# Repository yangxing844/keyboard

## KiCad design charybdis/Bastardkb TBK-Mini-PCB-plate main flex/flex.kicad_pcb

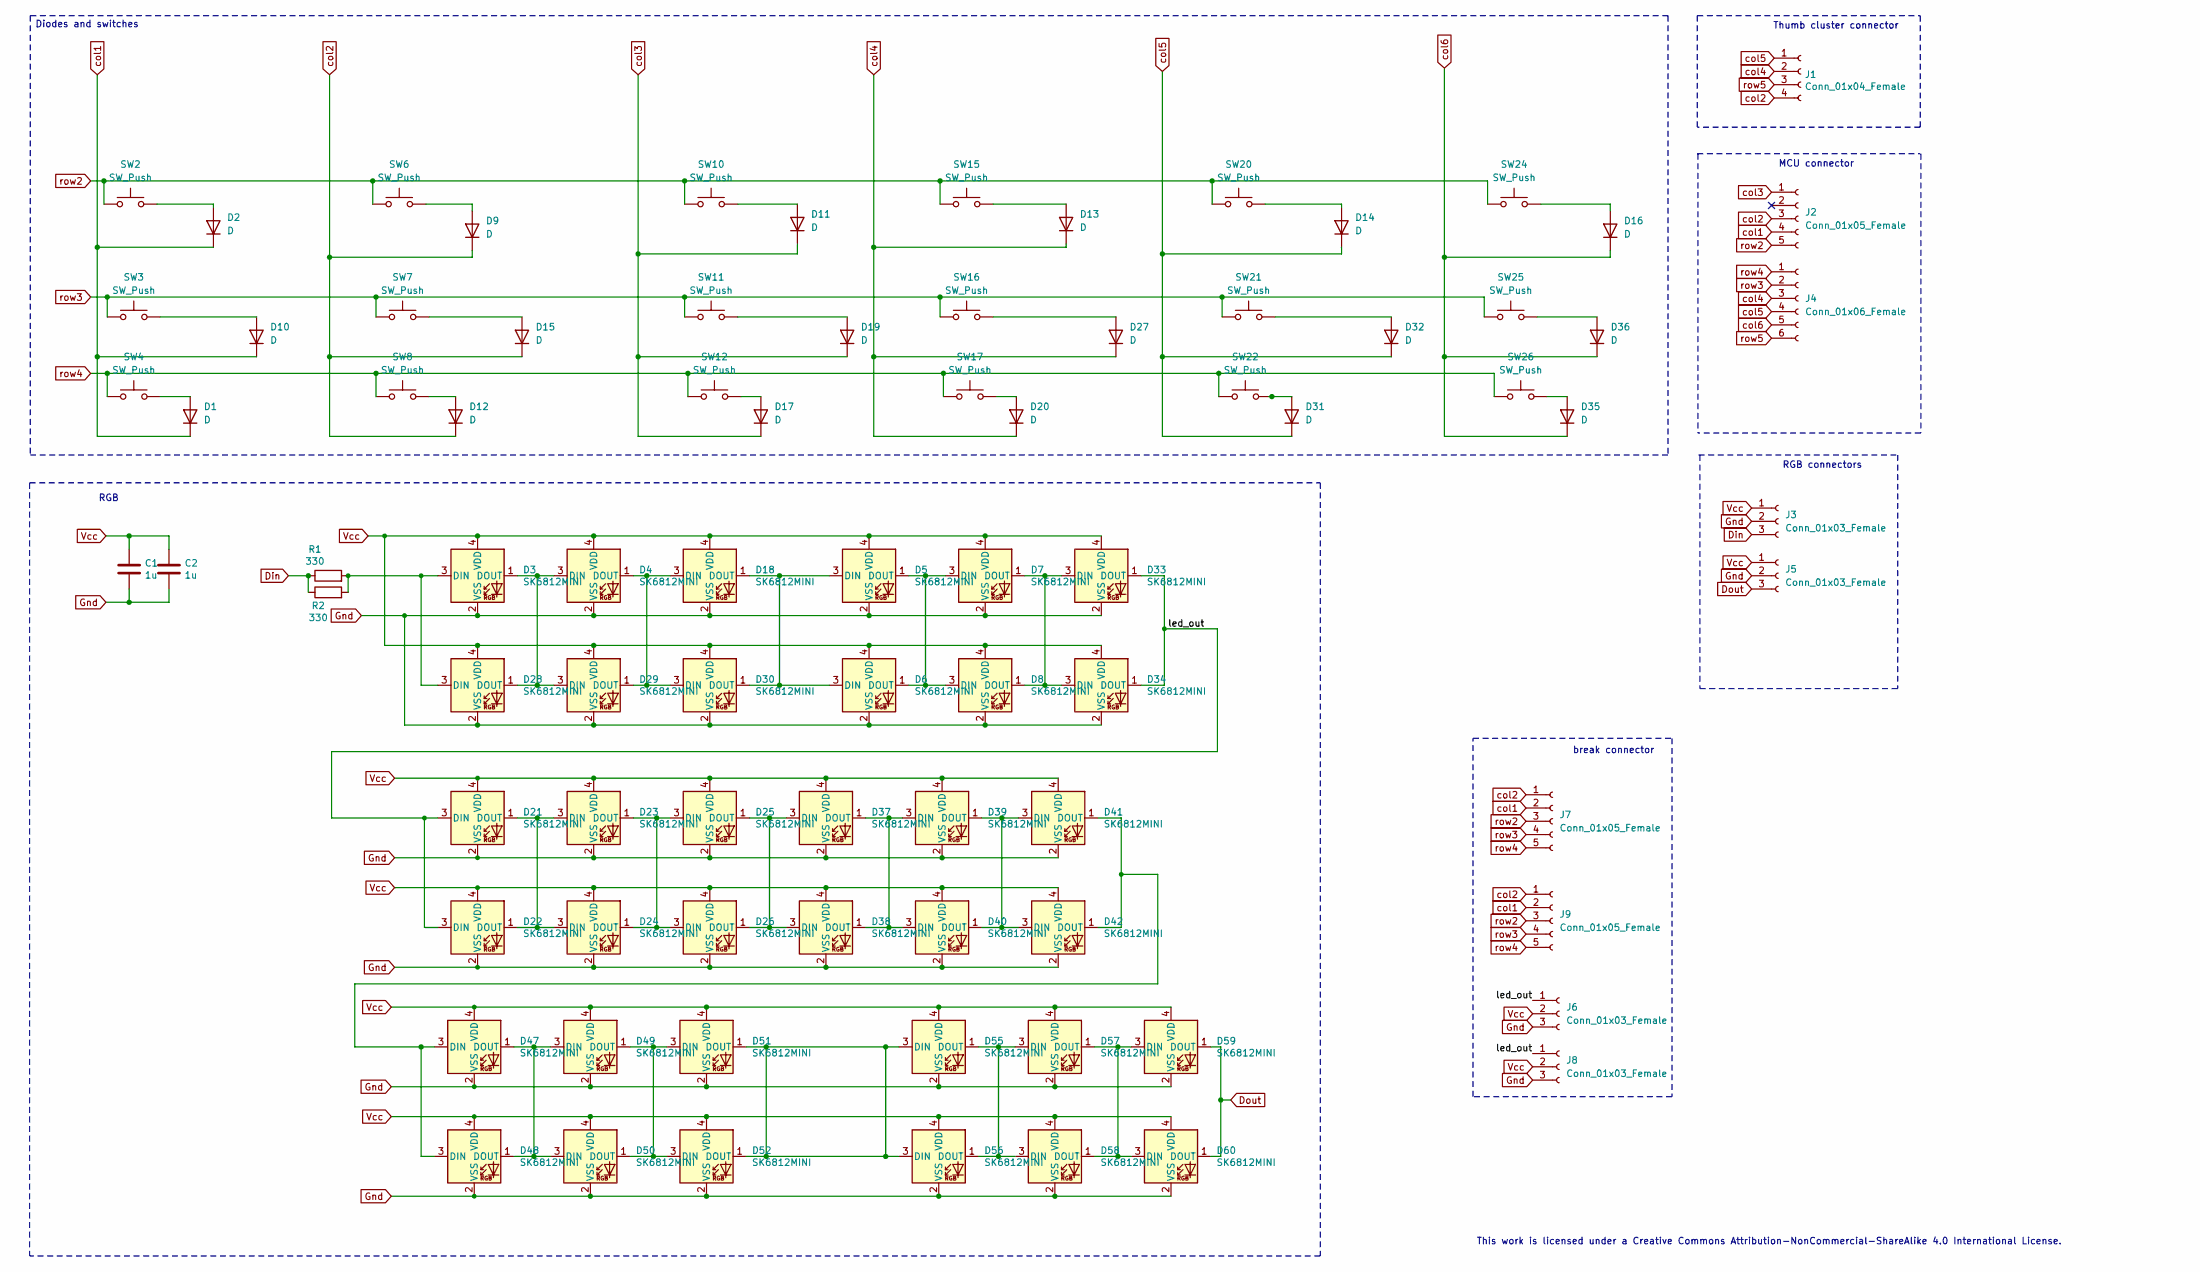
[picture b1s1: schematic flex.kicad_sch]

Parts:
C1, C2: 1u; C_1206_3216Metric_Pad1.42x1.75mm_HandSolder
D1, D2, D9, D10, D11, D12, D13, D14, D15, D16, D17, D19, D20, D27, D31, D32, D35, D36: D; Diode_TH_SOD123
D3, D4, D5, D7, D18, D21, D23, D25, D33, D37, D39, D41, D47, D49, D51, D55, D57, D59: SK6812MINI; YS-SK6812MINI-E_REVERSE
D6, D8, D22, D24, D26, D28, D29, D30, D34, D38, D40, D42, D48, D50, D52, D56, D58, D60: SK6812MINI; YS-SK6812MINI-E_REVERSE_NO_EDGECUT
J1: Conn_01x04_Female; PinHeader_1x04_P2.54mm_Vertical
J2, J7, J9: Conn_01x05_Female; PinHeader_1x05_P2.54mm_Vertical
J3, J5, J6, J8: Conn_01x03_Female; PinHeader_1x03_P2.54mm_Vertical
J4: Conn_01x06_Female; PinHeader_1x06_P2.54mm_Vertical
R1, R2: 330; R_1206_3216Metric_Pad1.42x1.75mm_HandSolder
SW2, SW3, SW4, SW6, SW7, SW8, SW10, SW11, SW12, SW15, SW16, SW17, SW20, SW21, SW22, SW24, SW25, SW26: SW_Push; keyswitch_cherrymx_hotswap_1u

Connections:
/led_out: D21.3 (DIN), D22.3 (DIN), D33.1 (DOUT), D34.1 (DOUT), J6.1, J8.1
Din: J3.3, R1.1, R2.1
Dout: D59.1 (DOUT), D60.1 (DOUT), J5.3
Gnd: C1.2, C2.2, D3.2 (VSS), D4.2 (VSS), D5.2 (VSS), D6.2 (VSS), D7.2 (VSS), D8.2 (VSS), D18.2 (VSS), D21.2 (VSS), D22.2 (VSS), D23.2 (VSS), D24.2 (VSS), D25.2 (VSS), D26.2 (VSS), D28.2 (VSS), D29.2 (VSS), D30.2 (VSS), D33.2 (VSS), D34.2 (VSS), D37.2 (VSS), D38.2 (VSS), D39.2 (VSS), D40.2 (VSS), D41.2 (VSS), D42.2 (VSS), D47.2 (VSS), D48.2 (VSS), D49.2 (VSS), D50.2 (VSS), D51.2 (VSS), D52.2 (VSS), D55.2 (VSS), D56.2 (VSS), D57.2 (VSS), D58.2 (VSS), D59.2 (VSS), D60.2 (VSS), J3.2, J5.2, J6.3, J8.3
unnamed: D1.2 (A), SW4.2
unnamed: D2.2 (A), SW2.2
unnamed: D5.1 (DOUT), D6.1 (DOUT), D7.3 (DIN), D8.3 (DIN)
unnamed: D9.2 (A), SW6.2
unnamed: D10.2 (A), SW3.2
unnamed: D11.2 (A), SW10.2
unnamed: D12.2 (A), SW8.2
unnamed: D13.2 (A), SW15.2
unnamed: D14.2 (A), SW20.2
unnamed: D15.2 (A), SW7.2
unnamed: D16.2 (A), SW24.2
unnamed: D17.2 (A), SW12.2
unnamed: D4.1 (DOUT), D18.3 (DIN), D29.1 (DOUT), D30.3 (DIN)
unnamed: D5.3 (DIN), D6.3 (DIN), D18.1 (DOUT), D30.1 (DOUT)
unnamed: D19.2 (A), SW11.2
unnamed: D20.2 (A), SW17.2
unnamed: D21.1 (DOUT), D22.1 (DOUT), D23.3 (DIN), D24.3 (DIN)
unnamed: D23.1 (DOUT), D24.1 (DOUT), D25.3 (DIN), D26.3 (DIN)
unnamed: D25.1 (DOUT), D26.1 (DOUT), D37.3 (DIN), D38.3 (DIN)
unnamed: D27.2 (A), SW16.2
unnamed: D3.3 (DIN), D28.3 (DIN), R1.2, R2.2
unnamed: D3.1 (DOUT), D4.3 (DIN), D28.1 (DOUT), D29.3 (DIN)
unnamed: D31.2 (A), SW22.2
unnamed: D32.2 (A), SW21.2
unnamed: D7.1 (DOUT), D8.1 (DOUT), D33.3 (DIN), D34.3 (DIN)
unnamed: D35.2 (A), SW26.2
unnamed: D36.2 (A), SW25.2
unnamed: D37.1 (DOUT), D38.1 (DOUT), D39.3 (DIN), D40.3 (DIN)
unnamed: D39.1 (DOUT), D40.1 (DOUT), D41.3 (DIN), D42.3 (DIN)
unnamed: D41.1 (DOUT), D42.1 (DOUT), D47.3 (DIN), D48.3 (DIN)
unnamed: D47.1 (DOUT), D48.1 (DOUT), D49.3 (DIN), D50.3 (DIN)
unnamed: D49.1 (DOUT), D50.1 (DOUT), D51.3 (DIN), D52.3 (DIN)
unnamed: D51.1 (DOUT), D52.1 (DOUT), D55.3 (DIN), D56.3 (DIN)
unnamed: D55.1 (DOUT), D56.1 (DOUT), D57.3 (DIN), D58.3 (DIN)
unnamed: D57.1 (DOUT), D58.1 (DOUT), D59.3 (DIN), D60.3 (DIN)
Vcc: C1.1, C2.1, D3.4 (VDD), D4.4 (VDD), D5.4 (VDD), D6.4 (VDD), D7.4 (VDD), D8.4 (VDD), D18.4 (VDD), D21.4 (VDD), D22.4 (VDD), D23.4 (VDD), D24.4 (VDD), D25.4 (VDD), D26.4 (VDD), D28.4 (VDD), D29.4 (VDD), D30.4 (VDD), D33.4 (VDD), D34.4 (VDD), D37.4 (VDD), D38.4 (VDD), D39.4 (VDD), D40.4 (VDD), D41.4 (VDD), D42.4 (VDD), D47.4 (VDD), D48.4 (VDD), D49.4 (VDD), D50.4 (VDD), D51.4 (VDD), D52.4 (VDD), D55.4 (VDD), D56.4 (VDD), D57.4 (VDD), D58.4 (VDD), D59.4 (VDD), D60.4 (VDD), J3.1, J5.1, J6.2, J8.2
col1: D1.1 (K), D2.1 (K), D10.1 (K), J2.4, J7.2, J9.2
col2: D9.1 (K), D12.1 (K), D15.1 (K), J1.4, J2.3, J7.1, J9.1
col3: D11.1 (K), D17.1 (K), D19.1 (K), J2.1
col4: D13.1 (K), D20.1 (K), D27.1 (K), J1.2, J4.3
col5: D14.1 (K), D31.1 (K), D32.1 (K), J1.1, J4.4
col6: D16.1 (K), D35.1 (K), D36.1 (K), J4.5
row2: J2.5, J7.3, J9.3, SW2.1, SW6.1, SW10.1, SW15.1, SW20.1, SW24.1
row3: J4.2, J7.4, J9.4, SW3.1, SW7.1, SW11.1, SW16.1, SW21.1, SW25.1
row4: J4.1, J7.5, J9.5, SW4.1, SW8.1, SW12.1, SW17.1, SW22.1, SW26.1
row5: J1.3, J4.6

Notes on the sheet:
break connector
RGB
Diodes and switches
Thumb cluster connector
RGB connectors
MCU connector
This work is licensed under a Creative Commons Attribution-NonCommercial-ShareAlike 4.0 International License.

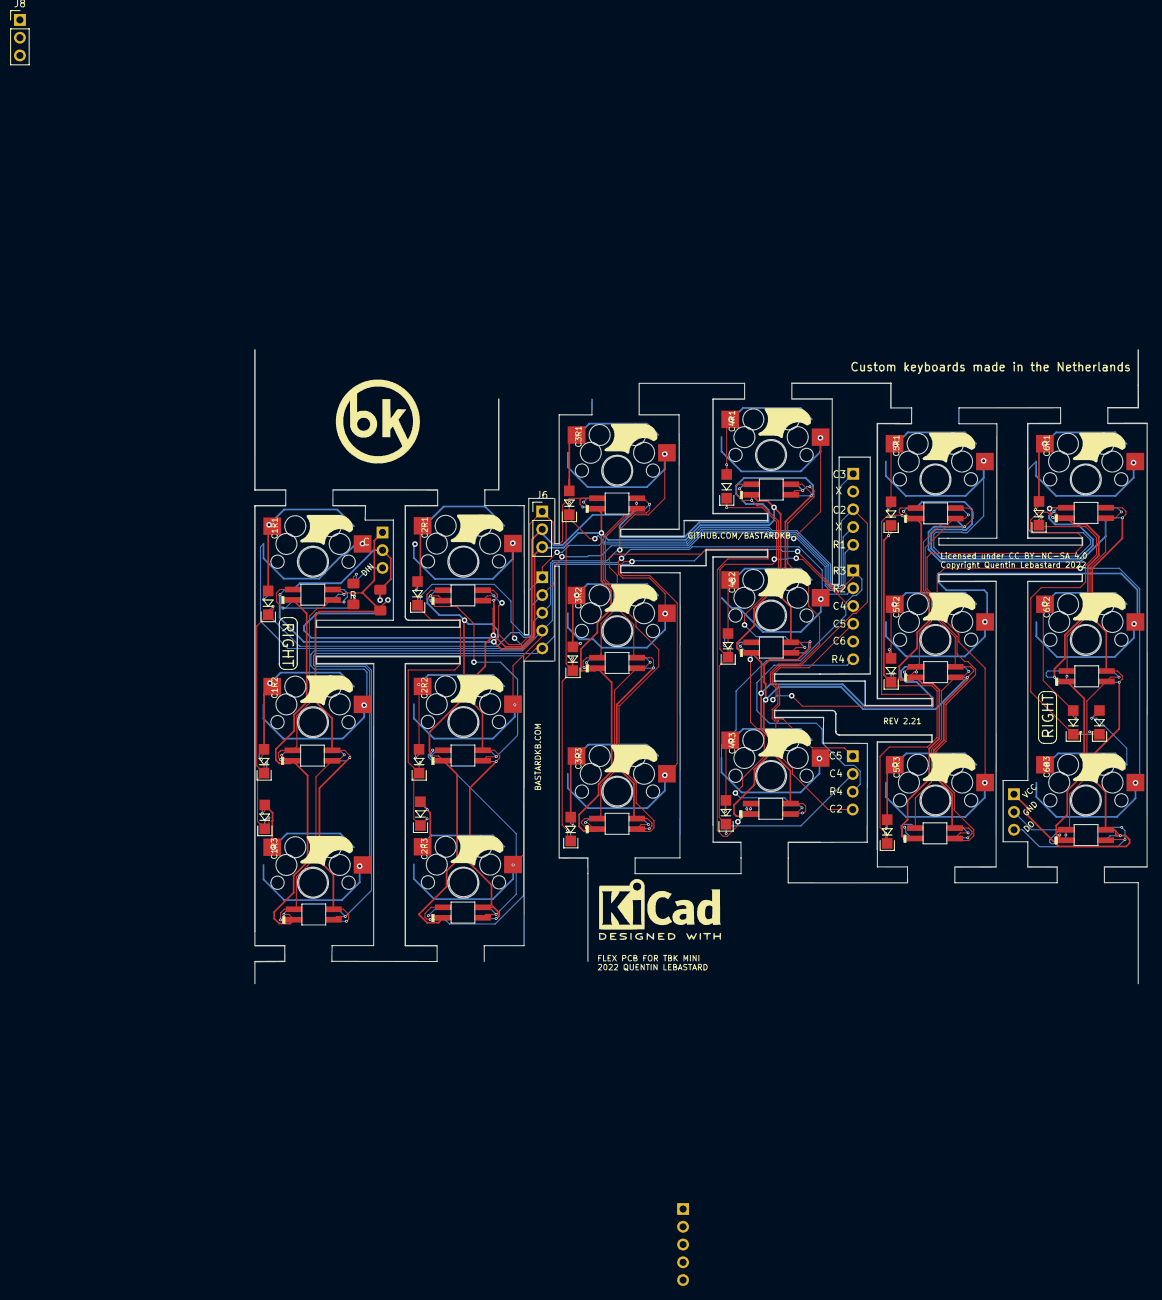
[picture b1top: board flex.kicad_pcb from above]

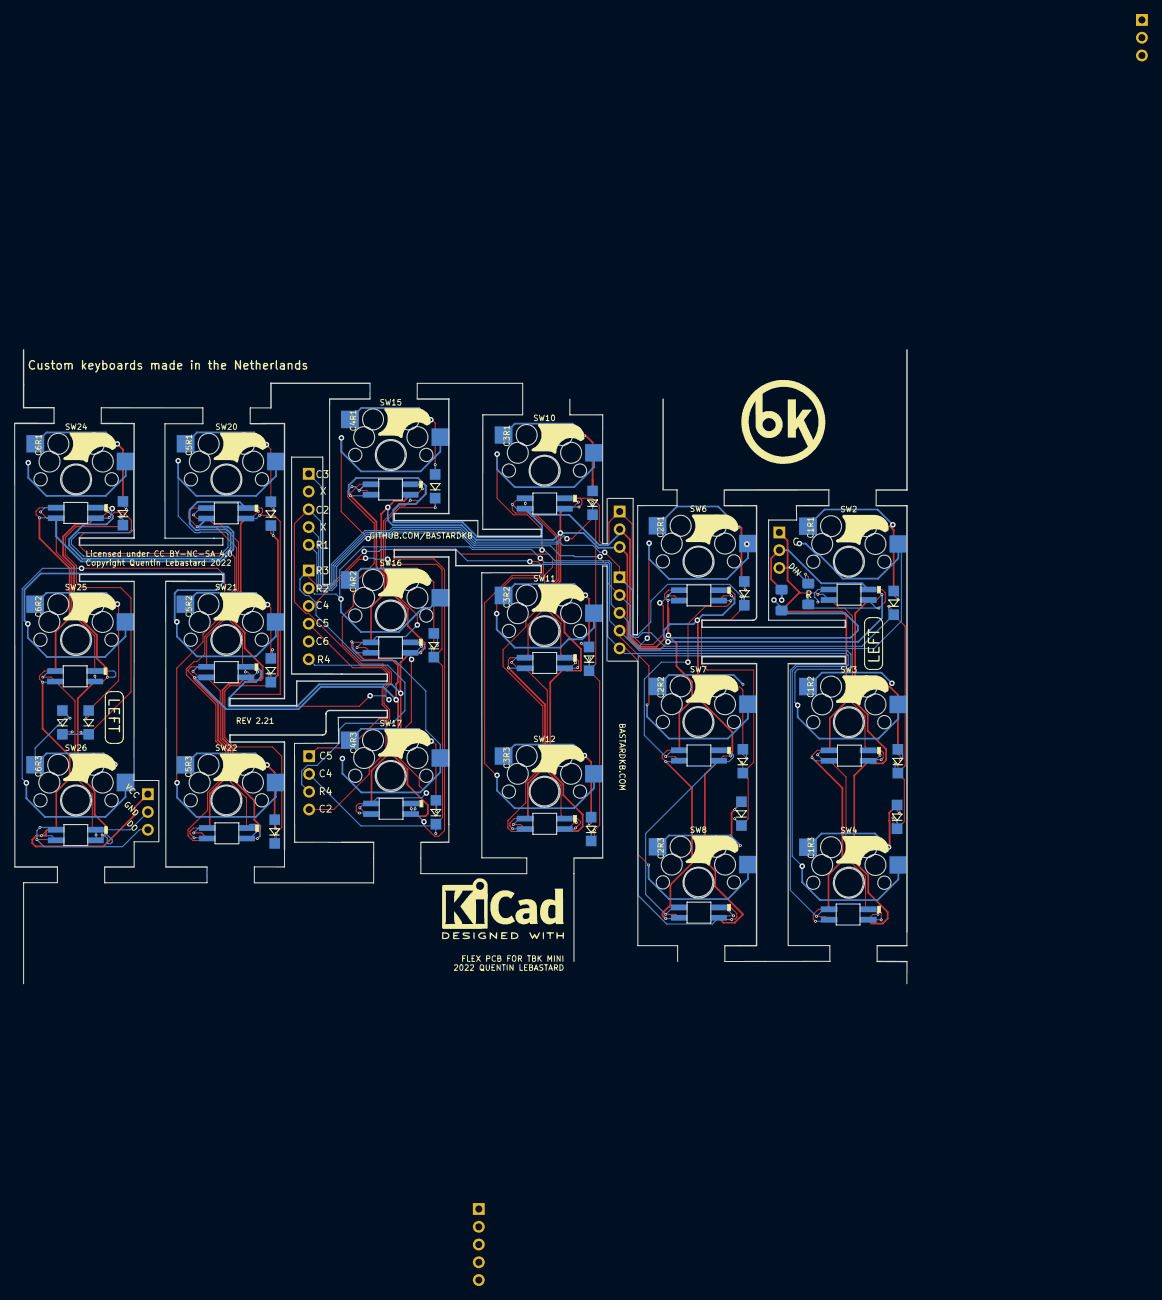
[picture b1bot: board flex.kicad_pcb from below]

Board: 2 copper layers, 127.6 x 90.6 mm, 85 parts (38 on the bottom side), 50 nets.

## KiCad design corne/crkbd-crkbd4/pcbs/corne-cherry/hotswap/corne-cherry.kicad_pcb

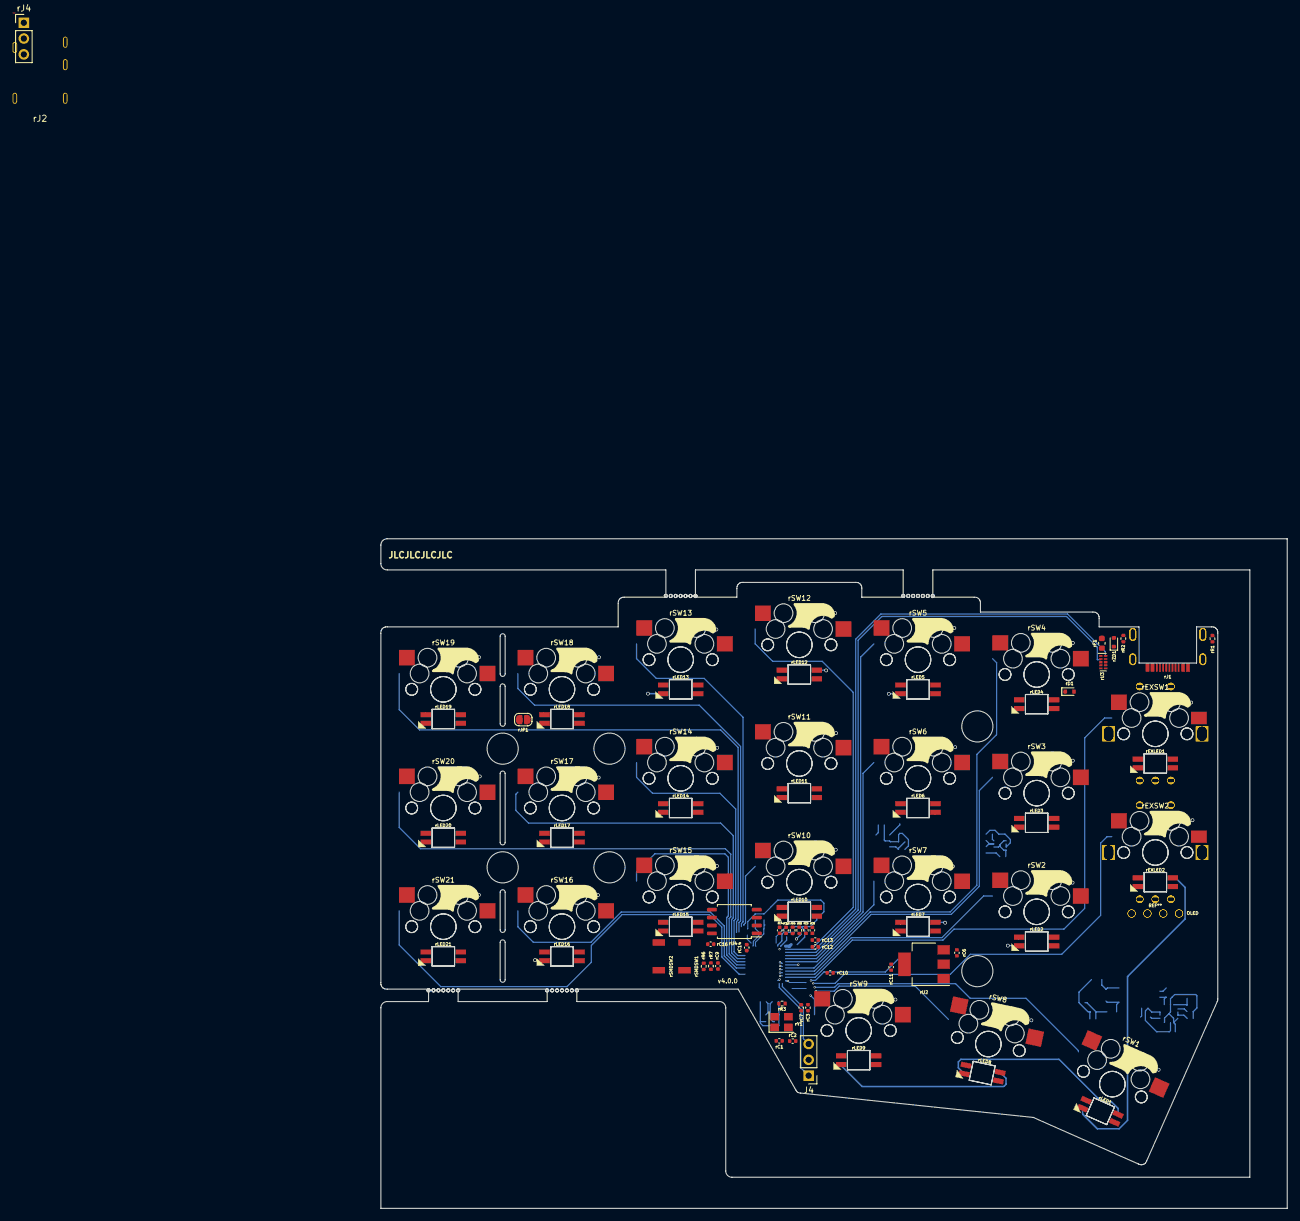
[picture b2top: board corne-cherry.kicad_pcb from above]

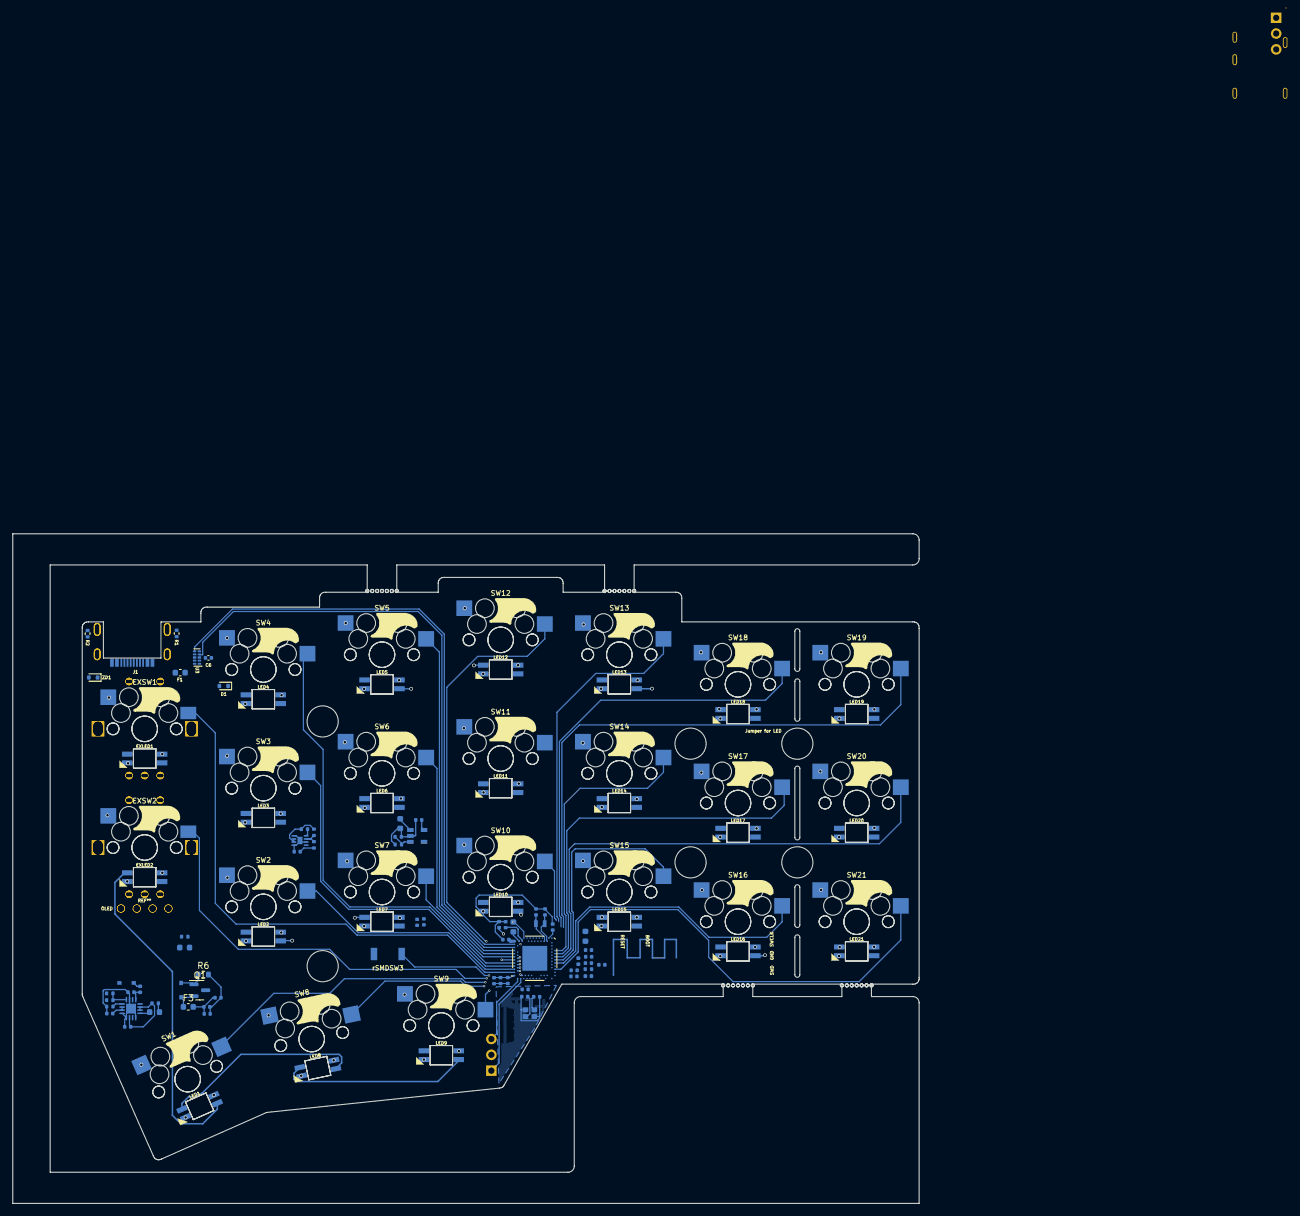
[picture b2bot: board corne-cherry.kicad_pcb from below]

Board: 4 copper layers, 145.5 x 107.5 mm, 208 parts (119 on the bottom side), 126 nets.

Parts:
AE1: Antenna; 2.4GHz-meander-antenna-v2
BT1, BT2, BT3, BT4: Breakaway Tabs; Breakaway_Tabs
C1, C2, C15, C17: 15pF; Capacitor_0402_1005M-nosilk
C3, C20, C25, C26, C27: 100nF; Capacitor_0402_1005M-nosilk
C4: 100pF; Capacitor_0402_1005M-nosilk
C5: 1nF; Capacitor_0402_1005M-nosilk
C6: 10u; C_0402_1005Metric
C7, C8, C19, C22, C23, C24, C28, C30: 4.7uF; Capacitor_0402_1005M-nosilk
C9, C16, C16#2, C21, C29: 1uF; Capacitor_0402_1005M-nosilk
C10: 47nF; Capacitor_0402_1005M-nosilk
C12: 1.5pF; Capacitor_0402_1005M-nosilk
C13, C14: 1pF; Capacitor_0402_1005M-nosilk
C18: 10uF; Capacitor_0603_1608M-nosilk
D1: 1N4148WT; D_SOD-523
D2, D5: PMEG4010CEJ; D_SOD-323F-nosilk
D3: ORANGE; LED_0603_1608Metric-nosilk
D4: BLUE; LED_0603_1608Metric-nosilk
EXLED1, EXLED2: YS-SK6812MINI-E
EXSW1, EXSW2: RotaryEncoder_Switch; keyswitch_cherrymx_hotswap_1u_rotary_encoder_ec12
F1, F3: BSMD0603-050-12V; Fuse_0603_1608Metric
F2: 500mA hold; Fuse_0402_1005Metric
J1: TYPE-C-31-M-13C
J3: Conn_01x04; OLED
J4: Conn_01x03; PinHeader_1x03_P2.54mm_Vertical
L1: 15nH; Inductor_0402_1005M-nosilk
L2, L3: 10uH; Inductor_0603_1608M-nosilk
L4: 3.9nH; Inductor_0402_1005M-nosilk
LED1, LED2, LED3, LED4, LED5, LED6, LED7, LED8, LED9, LED10, LED11, LED12, LED13, LED14, LED15, LED16, LED17, LED18, LED19, LED20, LED21: YS-SK6812MINI-E
NT1: NetTie_2; net-tie-2-tiny
Q1: AO3401A; SOT-23
R1, R2: 5.1k; R_0402_1005Metric
R3: 0R; Resistor_0402_1005M-nosilk
R4, R4#2: 2M; Resistor_0402_1005M-nosilk
R5, R5#2, R8, R10: 3.9k; Resistor_0402_1005M-nosilk
R6: 100; R_0603_1608Metric
R9, R11, R12: 10k; Resistor_0402_1005M-nosilk
R13: 1.5k; Resistor_0402_1005M-nosilk
SW1, SW2, SW3, SW4, SW5, SW6, SW7, SW8, SW9, SW10, SW11, SW12, SW13, SW14, SW15, SW16, SW17, SW18, SW19, SW20, SW21: SW_Push; keyswitch_cherrymx_hotswap_1u
U1: nRF52840; AQFN-73-1EP_7x7mm_P0.5mm_NRF52840-custom
U3: TPD4E05U06DQAR; USON-10_2.5x1.0mm_P0.5mm
U5: XC6220B331MR; SOT-23-5
U6: MAX17048; TDFN-8-1EP_2x2mm_P0.5mm_EP0.8x1.2mm
U7: BQ24075RGT; VQFN-16-1EP_3x3mm_P0.5mm_EP1.6x1.6mm
Y1: 32MHz; Crystal_SMD_2016-4Pin_2.0x1.6mm
Y2: 32.768 kHz; Crystal_SMD_2012-2Pin_2.0x1.2mm
ZD1: ESD5Z5V0C; D_SOD-523
rBT1, rBT2, rBT3, rBT4: Breakaway Tabs; Breakaway_Tabs
rC1, rC2: 27p; C_0402_1005Metric
rC3, rC4, rC7, rC9, rC10, rC12, rC13, rC14, rC15: 100n; C_0402_1005Metric
rC5, rC8, rC16: 1u; C_0402_1005Metric
rC6, rC11: 10u; C_0402_1005Metric
rD1: 1N4148WT; D_SOD-523
rEXLED1, rEXLED2: YS-SK6812MINI-E
rEXSW1, rEXSW2: RotaryEncoder_Switch; keyswitch_cherrymx_hotswap_1u_rotary_encoder_ec12
rF1: BSMD0603-050-12V; Fuse_0603_1608Metric
rJ1: TYPE-C-31-M-13C
rJ2: ST-0277D00-052-142
rJ3: Conn_01x04; OLED
rJ4: Conn_01x03; PinHeader_1x03_P2.54mm_Vertical
rJP1: SolderJumper_2_Bridged; SolderJumper-2_P1.3mm_Open_RoundedPad1.0x1.5mm
rLED1, rLED2, rLED3, rLED4, rLED5, rLED6, rLED7, rLED8, rLED9, rLED10, rLED11, rLED12, rLED13, rLED14, rLED15, rLED16, rLED17, rLED18, rLED19, rLED20, rLED21: YS-SK6812MINI-E
rR1, rR2: 5.1k; R_0402_1005Metric
rR3, rR6: 1k; R_0402_1005Metric
rR4, rR5: 27; R_0402_1005Metric
rR7: 10k; R_0402_1005Metric
rSMDSW1, rSMDSW2, rSMDSW3: TS-1088R-02026
rSW1, rSW2, rSW3, rSW4, rSW5, rSW6, rSW7, rSW8, rSW9, rSW10, rSW11, rSW12, rSW13, rSW14, rSW15, rSW16, rSW17, rSW18, rSW19, rSW20, rSW21: SW_Push; keyswitch_cherrymx_hotswap_1u
rU2: NCP1117LPST33T3G; SOT-223-3_TabPin2
rU3: TPD4E05U06DQAR; USON-10_2.5x1.0mm_P0.5mm
rU4: W25Q128JVSIQ; SOIC-8_5.23x5.23mm_P1.27mm
rY1: 12MHz 18pF; Crystal_SMD_3225-4Pin_3.2x2.5mm
rZD1: ESD5Z5V0C; D_SOD-523

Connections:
+1V1R: rC3.1, rC4.1, rC5.1
+3V3R: rC7.1, rC8.1, rC9.1, rC10.1, rC11.1, rC12.1, rC13.1, rC14.1, rC15.1, rC16.1, rR7.2, rU2.2 (VO), rU4.8 (VCC)
+5V: C6.1, D1.2 (A), D5.1 (K), F1.2, F3.1, J3.3, Q1.2 (S)
+5VR: rC6.1, rD1.2 (A), rF1.2, rJ2.T, rJ3.3, rU2.3 (VI)
/left/ANT: AE1.1 (A), C12.2, R3.2
/left/CS: EXSW1.B, EXSW2.B, U1.M2 (TRACECLK/P0.07)
/left/D+: J1.A6 (D+), J1.B6 (D+), U1.AD6 (D+), U3.1 (D1+), U3.4 (D2+), U3.7 (NC), U3.10 (NC)
/left/D-: J1.A7 (D-), J1.B7 (D-), U1.AD4 (D-), U3.2 (D1-), U3.5 (D2-), U3.6 (NC), U3.9 (NC)
/left/KEY1: SW1.1, U1.AC17 (P0.21)
/left/KEY2: SW2.1, U1.AD20 (P0.24)
/left/KEY3: SW3.1, U1.AD18 (P0.22)
/left/KEY4: SW4.1, U1.AD16 (P0.20)
/left/KEY5: SW5.1, U1.AD8 (P0.13)
/left/KEY6: SW6.1, U1.AD10 (P0.15)
/left/KEY7: SW7.1, U1.AD12 (P0.17)
/left/KEY8: SW8.1, U1.AC19 (P0.23)
/left/KEY9: SW9.1, U1.AC21 (P0.25)
/left/KEY10: SW10.1, U1.U24 (P1.04)
/left/KEY11: SW11.1, U1.W24 (P1.02)
/left/KEY12: SW12.1, U1.Y23 (P1.01)
/left/KEY13: SW13.1, U1.R24 (P1.06)
/left/KEY14: SW14.1, U1.A8 (AIN7/P0.31)
/left/KEY15: SW15.1, U1.A14 (P1.15)
/left/KEY16: SW16.1, U1.A16 (P1.13)
/left/KEY17: SW17.1, U1.A10 (AIN5/P0.29)
/left/KEY18: SW18.1, U1.L24 (NFC1/P0.09)
/left/KEY19: SW19.1, U1.J24 (NFC2/P0.10)
/left/KEY20: SW20.1, U1.A12 (AIN0/P0.02)
/left/KEY21: SW21.1, U1.A20 (P1.10)
/left/KEYEX1: EXSW1.S2, U1.AD22 (TRACEDATA0/P1.00)
/left/KEYEX2: EXSW2.S2, U1.AC15 (P0.19)
/left/RE0A: EXSW1.A, J3.1, U1.K2 (AIN3/P0.05)
/left/RE1A: EXSW2.A, J3.2, U1.H2 (P0.27)
/left/SWC: J4.1, U1.AA24 (SWDCLK)
/left/SWD: J4.3, U1.AC24 (SWDIO)
/right/D+: rJ1.A6 (D+), rJ1.B6 (D+), rR4.1, rU3.1 (D1+), rU3.4 (D2+), rU3.7 (NC), rU3.10 (NC)
/right/D-: rJ1.A7 (D-), rJ1.B7 (D-), rR5.2, rU3.2 (D1-), rU3.5 (D2-), rU3.6 (NC), rU3.9 (NC)
/right/QSPI_SS: rR6.1, rR7.1, rU4.1 (~CS)
/right/RE1A: rEXSW2.A, rJ3.1
/right/REB: rEXSW1.B, rEXSW2.B, rJ3.2
BAT_I2C_SCL: R5.1, R5#2.1, U1.R1 (TRACEDATA3/P1.09), U6.7 (SCL)
BAT_I2C_SDA: R8.1, U1.U1 (TRACEDATA1/P0.12), U6.8 (SDA)
BLUE_LED: D4.2 (A), U1.G1 (P0.26)
CHARGE_CTRL_1: R9.1, U1.L1 (P0.06)
CHARGE_CTRL_2: R10.2, U1.N1 (P0.08)
EXT_5V: D2.1 (K), F2.2
GND: C1.2, C2.2, C3.2, C4.2, C5.2, C6.2, C7.2, C8.1, C9.1, C10.1, C12.1, C13.1, C15.1, C16.2, C16#2.2, C17.1, C18.1, C19.1, C20.1, C21.2, C22.1, C23.1, C24.1, C25.1, C26.1, C27.1, C28.1, C29.1, C30.2, EXLED1.3 (VSS), EXLED2.3 (VSS), EXSW1.C, EXSW1.S1, EXSW2.C, EXSW2.S1, J1.A1 (GND), J1.A12 (GND), J1.B1 (GND), J1.B12 (GND), J1.S1 (SHIELD), J3.4, J4.2, LED1.3 (VSS), LED2.3 (VSS), LED3.3 (VSS), LED4.3 (VSS), LED5.3 (VSS), LED6.3 (VSS), LED7.3 (VSS), LED8.3 (VSS), LED9.3 (VSS), LED10.3 (VSS), LED11.3 (VSS), LED12.3 (VSS), LED13.3 (VSS), LED14.3 (VSS), LED15.3 (VSS), LED16.3 (VSS), LED17.3 (VSS), LED18.3 (VSS), LED19.3 (VSS), LED20.3 (VSS), LED21.3 (VSS), NT1.2, R1.1, R2.1, R4.2, R4#2.2, R6.2, R12.2, R13.1, SW1.2, SW2.2, SW3.2, SW4.2, SW5.2, SW6.2, SW7.2, SW8.2, SW9.2, SW10.2, SW11.2, SW12.2, SW13.2, SW14.2, SW15.2, SW16.2, SW17.2, SW18.2, SW19.2, SW20.2, SW21.2, U1.B7 (VSS), U1.EP (VSS), U3.3 (GND), U3.8 (GND), U5.2 (GND), U6.1 (CTG), U6.4 (GND), U6.6 (QSTRT), U6.9 (EP), U7.4 (~CE), U7.5 (EN2), U7.8 (VSS), U7.15 (SYSOFF), U7.17 (VSS), Y1.2, Y1.4, ZD1.2 (A), rSMDSW3.1
GNDR: rC1.2, rC2.2, rC3.2, rC4.2, rC5.2, rC6.2, rC7.2, rC8.2, rC9.2, rC10.2, rC11.2, rC12.2, rC13.2, rC14.2, rC15.2, rC16.2, rEXLED1.3 (VSS), rEXLED2.3 (VSS), rEXSW1.C, rEXSW1.S1, rEXSW2.C, rEXSW2.S1, rJ1.A1 (GND), rJ1.A12 (GND), rJ1.B1 (GND), rJ1.B12 (GND), rJ1.S1 (SHIELD), rJ2.S, rJ3.4, rJ4.2, rLED1.3 (VSS), rLED2.3 (VSS), rLED3.3 (VSS), rLED4.3 (VSS), rLED5.3 (VSS), rLED6.3 (VSS), rLED7.3 (VSS), rLED8.3 (VSS), rLED9.3 (VSS), rLED10.3 (VSS), rLED11.3 (VSS), rLED12.3 (VSS), rLED13.3 (VSS), rLED14.3 (VSS), rLED15.3 (VSS), rLED16.3 (VSS), rLED17.3 (VSS), rLED18.3 (VSS), rLED19.3 (VSS), rLED20.3 (VSS), rLED21.3 (VSS), rR1.1, rR2.1, rSMDSW1.1, rSMDSW2.1, rSW1.2, rSW2.2, rSW3.2, rSW4.2, rSW5.2, rSW6.2, rSW7.2, rSW8.2, rSW9.2, rSW10.2, rSW11.2, rSW12.2, rSW13.2, rSW14.2, rSW15.2, rSW16.2, rSW17.2, rSW18.2, rSW19.2, rSW20.2, rSW21.2, rU2.1 (GND), rU3.3 (GND), rU3.8 (GND), rU4.4 (GND), rY1.2, rY1.4, rZD1.2 (A)
unnamed: C13.2, L4.1, R3.1
unnamed: D1.1 (K), EXLED1.1 (VDD), EXLED2.1 (VDD), LED1.1 (VDD), LED2.1 (VDD), LED3.1 (VDD), LED4.1 (VDD), LED5.1 (VDD), LED6.1 (VDD), LED7.1 (VDD), LED8.1 (VDD), LED9.1 (VDD), LED10.1 (VDD), LED11.1 (VDD), LED12.1 (VDD), LED13.1 (VDD), LED14.1 (VDD), LED15.1 (VDD), LED16.1 (VDD), LED17.1 (VDD), LED18.1 (VDD), LED19.1 (VDD), LED20.1 (VDD), LED21.1 (VDD)
unnamed: D3.2 (A), R11.2
unnamed: D3.1 (K), U7.9 (~CHG)
unnamed: D4.1 (K), R13.2
unnamed: D5.2 (A), Q1.1 (G), R6.1
unnamed: EXLED1.4 (DIN), EXLED2.2 (DOUT)
unnamed: EXLED1.2 (DOUT), LED4.4 (DIN)
unnamed: EXLED2.4 (DIN), LED1.2 (DOUT)
unnamed: J1.A5 (CC1), R1.2
unnamed: J1.B5 (CC2), R2.2
unnamed: L1.2, L2.1
unnamed: LED1.4 (DIN), LED8.2 (DOUT)
unnamed: LED2.4 (DIN), LED3.2 (DOUT)
unnamed: LED2.2 (DOUT), LED7.4 (DIN)
unnamed: LED3.4 (DIN), LED4.2 (DOUT)
unnamed: LED5.4 (DIN), LED6.2 (DOUT)
unnamed: LED6.4 (DIN), LED7.2 (DOUT)
unnamed: LED8.4 (DIN), LED9.2 (DOUT)
unnamed: LED10.4 (DIN), LED11.2 (DOUT)
unnamed: LED10.2 (DOUT), LED15.4 (DIN)
unnamed: LED11.4 (DIN), LED12.2 (DOUT)
unnamed: LED5.2 (DOUT), LED12.4 (DIN)
unnamed: LED13.4 (DIN), LED14.2 (DOUT)
unnamed: LED13.2 (DOUT), LED18.4 (DIN)
unnamed: LED14.4 (DIN), LED15.2 (DOUT)
unnamed: LED16.4 (DIN), LED17.2 (DOUT)
unnamed: LED16.2 (DOUT), LED21.4 (DIN)
unnamed: LED17.4 (DIN), LED18.2 (DOUT)
unnamed: LED19.4 (DIN), LED20.2 (DOUT)
unnamed: LED20.4 (DIN), LED21.2 (DOUT)
unnamed: C14.2, L4.2, U1.H23 (ANT)
unnamed: L2.2, U1.B3 (DCC)
unnamed: L3.2, U1.AB2 (DCCH)
unnamed: C3.1, U1.C1 (DEC1)
unnamed: C4.1, U1.D23 (DEC3)
unnamed: C9.2, C10.2, L1.1, U1.B5 (DEC4), U1.E24 (DEC6)
unnamed: C5.1, U1.N24 (DEC5)
unnamed: C7.1, U1.AC5 (DECUSB)
unnamed: U1.AC13 (P0.18/~RESET), rSMDSW3.2
unnamed: C1.1, U1.B24 (XC1), Y1.1
unnamed: C2.1, U1.A23 (XC2), Y1.3
unnamed: C15.2, U1.D2 (XL1/P0.00), Y2.1
unnamed: C17.2, U1.F2 (XL2/P0.01), Y2.2
unnamed: C21.1, F2.1, U7.13 (IN)
unnamed: R9.2, R10.1, U7.16 (ISET)
unnamed: R12.1, U7.1 (TS)
unnamed: rC2.1, rR3.1, rY1.3
unnamed: rD1.1 (K), rEXLED1.1 (VDD), rEXLED2.1 (VDD), rLED1.1 (VDD), rLED2.1 (VDD), rLED3.1 (VDD), rLED4.1 (VDD), rLED5.1 (VDD), rLED6.1 (VDD), rLED7.1 (VDD), rLED8.1 (VDD), rLED9.1 (VDD), rLED10.1 (VDD), rLED11.1 (VDD), rLED12.1 (VDD), rLED13.1 (VDD), rLED14.1 (VDD), rLED15.1 (VDD), rLED16.1 (VDD), rLED17.1 (VDD), rLED18.1 (VDD), rLED19.1 (VDD), rLED20.1 (VDD), rLED21.1 (VDD)
unnamed: rEXLED1.2 (DOUT), rEXLED2.4 (DIN)
unnamed: rEXLED2.2 (DOUT), rLED1.4 (DIN)
unnamed: rJ1.A5 (CC1), rR1.2
unnamed: rJ1.B5 (CC2), rR2.2
unnamed: rLED1.2 (DOUT), rLED2.4 (DIN)
unnamed: rLED2.2 (DOUT), rLED3.4 (DIN)
unnamed: rLED3.2 (DOUT), rLED4.4 (DIN)
unnamed: rLED4.2 (DOUT), rLED5.4 (DIN)
unnamed: rLED5.2 (DOUT), rLED6.4 (DIN)
unnamed: rLED6.2 (DOUT), rLED7.4 (DIN)
unnamed: rLED7.2 (DOUT), rLED8.4 (DIN)
unnamed: rLED8.2 (DOUT), rLED9.4 (DIN)
unnamed: rLED9.2 (DOUT), rLED10.4 (DIN)
unnamed: rLED10.2 (DOUT), rLED11.4 (DIN)
unnamed: rLED11.2 (DOUT), rLED12.4 (DIN)
unnamed: rLED12.2 (DOUT), rLED13.4 (DIN)
unnamed: rLED13.2 (DOUT), rLED14.4 (DIN)
unnamed: rLED14.2 (DOUT), rLED15.4 (DIN)
unnamed: rLED15.2 (DOUT), rLED16.4 (DIN)
unnamed: rR6.2, rSMDSW1.2
unnamed: rC1.1, rY1.1
PPH_VCC: C19.2, U5.5 (VOUT)
PPH_VCC_CTRL: R4.1, R4#2.1, U1.J1 (AIN2/P0.04), U5.3 (CE)
VBAT: C16.1, C16#2.1, C20.2, C23.2, C30.1, F3.2, R5.2, R5#2.2, R8.2, U6.2 (CELL), U6.3 (VDD), U7.2 (BAT), U7.3 (BAT)
VBUS: C8.2, D2.2 (A), F1.1, J1.A4 (VBUS), J1.A9 (VBUS), J1.B4 (VBUS), J1.B9 (VBUS), U1.AD2 (VBUS), ZD1.1 (K)
VBUSR: rF1.1, rJ1.A4 (VBUS), rJ1.A9 (VBUS), rJ1.B4 (VBUS), rJ1.B9 (VBUS), rZD1.1 (K)
VDDH: C18.2, C22.2, C24.2, R11.1, U1.Y2 (VDDH), U5.1 (VIN), U7.6 (EN1), U7.10 (OUT), U7.11 (OUT)
VDD_NRF: C25.2, C26.2, C27.2, C28.2, C29.2, L3.1, U1.A22 (VDD), U1.AD14 (VDD), U1.AD23 (VDD), U1.B1 (VDD), U1.W1 (VDD)
VSS_PA: C14.1, NT1.1, U1.F23 (VSS_PA)

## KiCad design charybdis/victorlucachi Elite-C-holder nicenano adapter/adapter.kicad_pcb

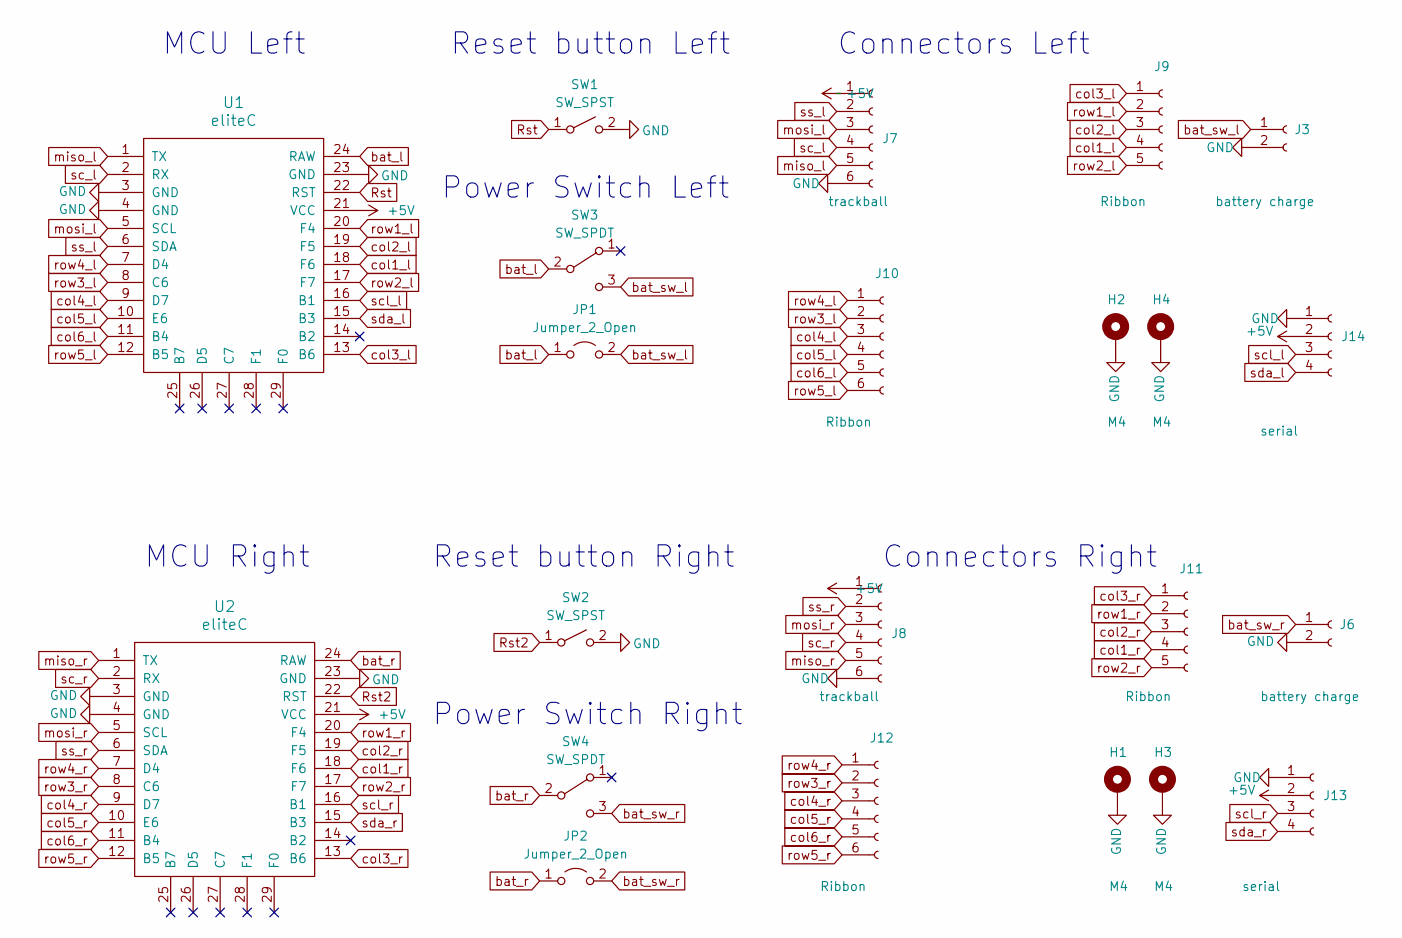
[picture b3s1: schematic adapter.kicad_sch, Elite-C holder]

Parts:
H1, H2, H3, H4: M4; MountingHole_4mm_Pad_thin
J3, J6: battery charge; JST_PH_B2B-PH-K_1x02_P2.00mm_Vertical
J7, J8: trackball; 6_PinHeader
J9, J11: Ribbon; 5_PinHeader
J10, J12: Ribbon; 6_PinHeader
J13, J14: serial; PinHeader_1x04_P2.54mm_Vertical
JP1, JP2: Jumper_2_Open; power_switch_jumper
SW1, SW2: SW_SPST; PushSwitch
SW3, SW4: SW_SPDT; SW_SPDT+H-MSK12C01_hor(7pin_SMD)
U1, U2: eliteC; Elite-C

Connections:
+5V: J7.1, J8.1, J13.2, J14.2, U1.21 (VCC), U2.21 (VCC)
GND: H1.1, H2.1, H3.1, H4.1, J3.2, J6.2, J7.6, J8.6, J13.1, J14.1, SW1.2 (B), SW2.2 (B), U1.3 (GND), U1.4 (GND), U1.23 (GND), U2.3 (GND), U2.4 (GND), U2.23 (GND)
Rst: SW1.1 (A), U1.22 (RST)
Rst2: SW2.1 (A), U2.22 (RST)
bat_l: JP1.1 (A), SW3.2 (B), U1.24 (RAW)
bat_r: JP2.1 (A), SW4.2 (B), U2.24 (RAW)
bat_sw_l: J3.1, JP1.2 (B), SW3.3 (C)
bat_sw_r: J6.1, JP2.2 (B), SW4.3 (C)
col1_l: J9.4, U1.18 (F6)
col1_r: J11.4, U2.18 (F6)
col2_l: J9.3, U1.19 (F5)
col2_r: J11.3, U2.19 (F5)
col3_l: J9.1, U1.13 (B6)
col3_r: J11.1, U2.13 (B6)
col4_l: J10.3, U1.9 (D7)
col4_r: J12.3, U2.9 (D7)
col5_l: J10.4, U1.10 (E6)
col5_r: J12.4, U2.10 (E6)
col6_l: J10.5, U1.11 (B4)
col6_r: J12.5, U2.11 (B4)
miso_l: J7.5, U1.1 (TX)
miso_r: J8.5, U2.1 (TX)
mosi_l: J7.3, U1.5 (SCL)
mosi_r: J8.3, U2.5 (SCL)
row1_l: J9.2, U1.20 (F4)
row1_r: J11.2, U2.20 (F4)
row2_l: J9.5, U1.17 (F7)
row2_r: J11.5, U2.17 (F7)
row3_l: J10.2, U1.8 (C6)
row3_r: J12.2, U2.8 (C6)
row4_l: J10.1, U1.7 (D4)
row4_r: J12.1, U2.7 (D4)
row5_l: J10.6, U1.12 (B5)
row5_r: J12.6, U2.12 (B5)
sc_l: J7.4, U1.2 (RX)
sc_r: J8.4, U2.2 (RX)
scl_l: J14.3, U1.16 (B1)
scl_r: J13.3, U2.16 (B1)
sda_l: J14.4, U1.15 (B3)
sda_r: J13.4, U2.15 (B3)
ss_l: J7.2, U1.6 (SDA)
ss_r: J8.2, U2.6 (SDA)

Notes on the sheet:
Power Switch Right
Reset button Left
Power Switch Left
Connectors Left
Reset button Right
MCU Left
MCU Right
Connectors Right

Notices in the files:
charybdis/Bastardkb TBK-Mini-PCB-plate main flex/flex.kicad_pcb:
Licensed under CC BY-NC-SA 4.0
Copyright Quentin Lebastard 2022
charybdis/Bastardkb TBK-Mini-PCB-plate main flex/flex.kicad_sch:
CC BY-NC-SA 4.0
charybdis/victorlucachi Elite-C-holder nicenano adapter/adapter.kicad_sch:
Licensed under CERN-OHL-W v2
